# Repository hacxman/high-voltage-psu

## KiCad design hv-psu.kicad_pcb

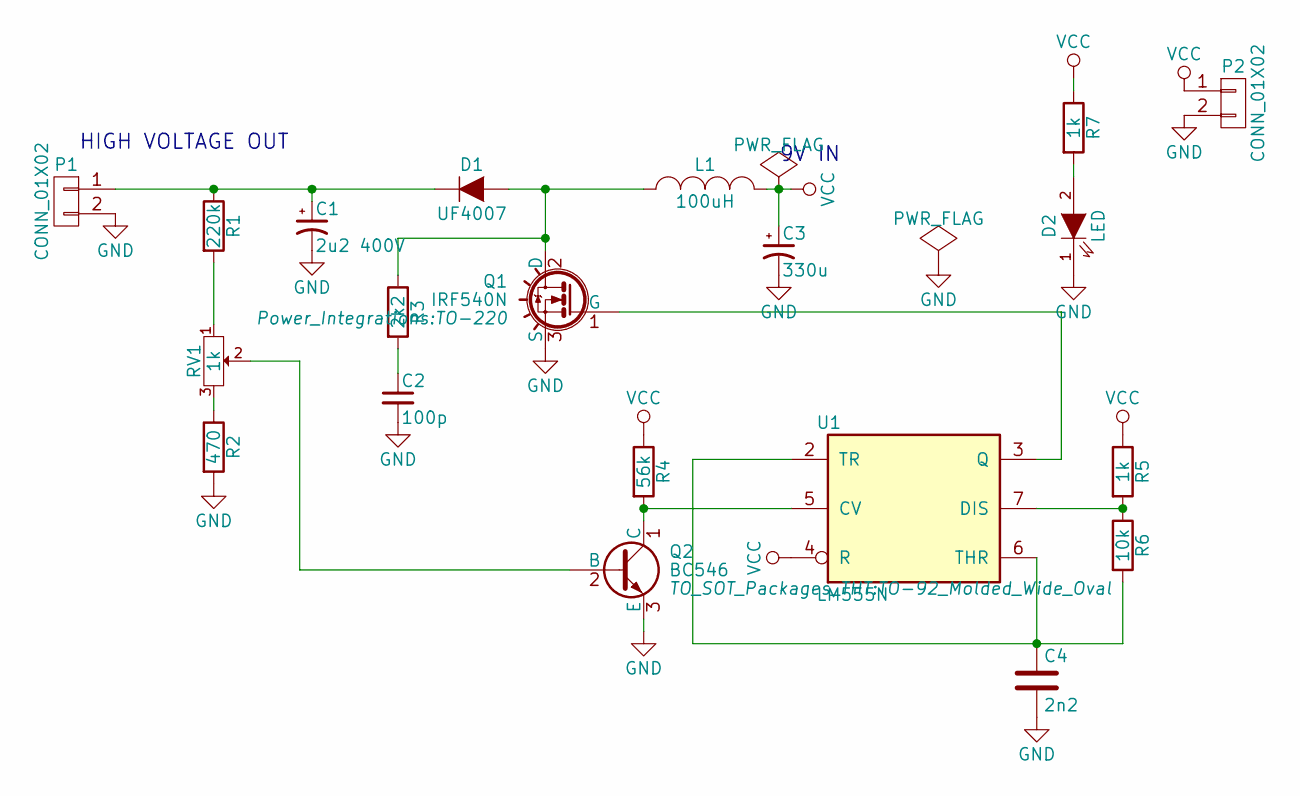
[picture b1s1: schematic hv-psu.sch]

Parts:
C1: 2u2 400V; C_Radial_D14_L31.5_P5
C2: 100p; C_Rect_L7_W2.5_P5
C3: 330u; C_Radial_D14_L31.5_P5
C4: 2n2; C_Rect_L7_W2.5_P5
D1: UF4007; Diode_DO-35_SOD27_Horizontal_RM10
D2: LED; LED-5MM
L1: 100uH; Choke_SMD_10.4x10.4_H4.8
P1, P2: CONN_01X02; TerminalBlock_Pheonix_MPT-2.54mm_2pol
Q1: IRF540N; TO-220
Q2: BC546; TO-92_Molded_Wide_Oval
R1: 220k; Resistor_Horizontal_RM10mm
R2: 470; Resistor_Horizontal_RM10mm
R3: 2k2; Resistor_Horizontal_RM10mm
R4: 56k; Resistor_Horizontal_RM10mm
R5, R7: 1k; Resistor_Horizontal_RM10mm
R6: 10k; Resistor_Horizontal_RM10mm
RV1: 1k; Potentiometer_WirePads_largePads
U1: LM555N; DIP-8_W7.62mm_LongPads

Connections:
GND: C1.2, C2.2, C3.2, C4.2, D2.1 (K), P1.2, P2.2, Q1.3 (S), Q2.3 (E), R2.2, U1.1 (GND)
unnamed: C1.1, D1.1 (K), P1.1, R1.1
unnamed: C2.1, R3.2
unnamed: C4.1, R6.2, U1.2 (TR), U1.6 (THR)
unnamed: D1.2 (A), L1.1, Q1.2 (D), R3.1
unnamed: D2.2 (A), R7.2
unnamed: Q1.1 (G), U1.3 (Q)
unnamed: Q2.1 (C), R4.2, U1.5 (CV)
unnamed: Q2.2 (B), RV1.2
unnamed: R1.2, RV1.1
unnamed: R2.1, RV1.3
unnamed: R5.2, R6.1, U1.7 (DIS)
VCC: C3.1, L1.2, P2.1, R4.1, R5.1, R7.1, U1.4 (R), U1.8 (VCC)

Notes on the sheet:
HIGH VOLTAGE OUT
9V IN

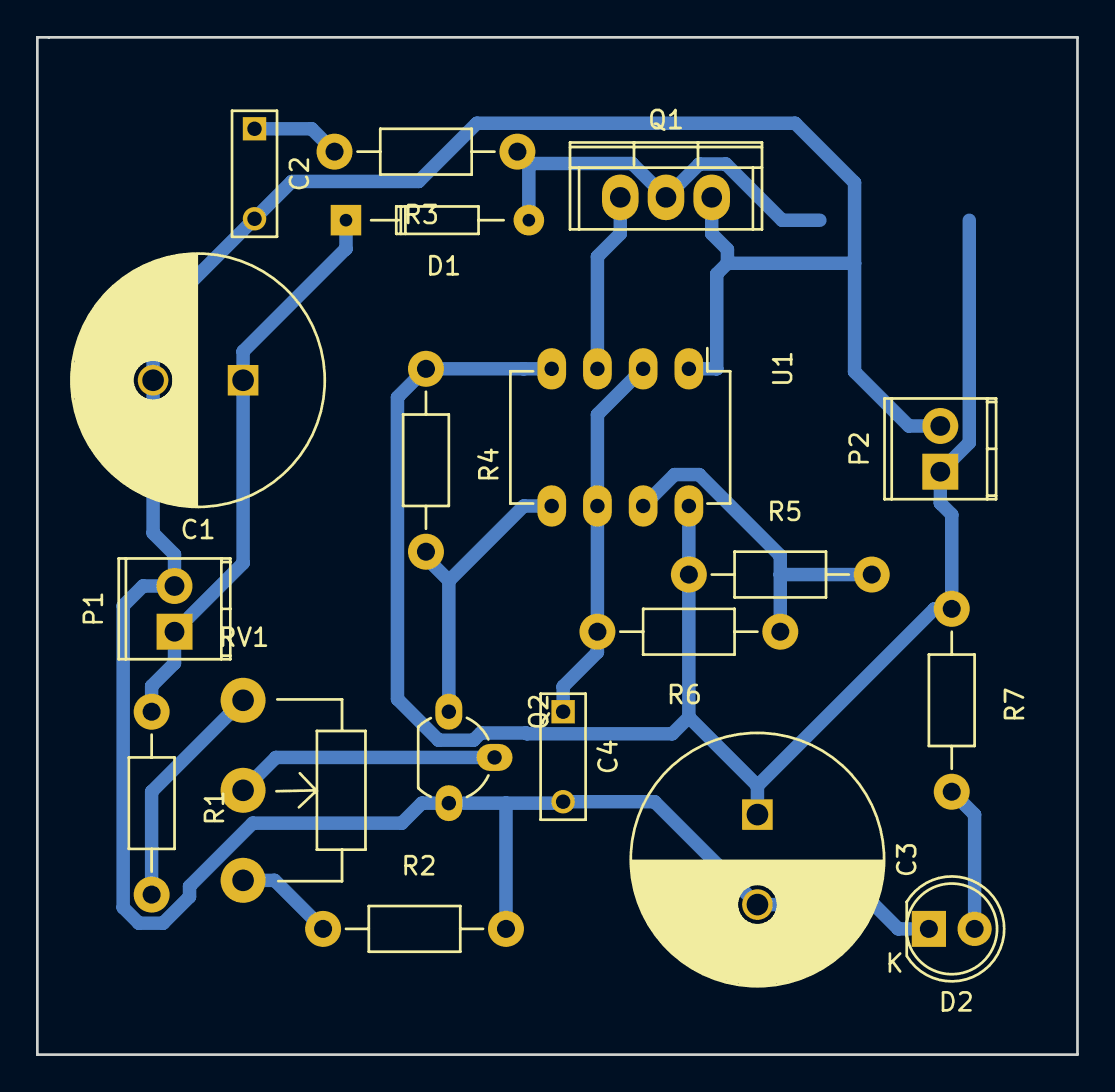
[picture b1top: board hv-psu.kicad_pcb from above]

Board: 2 copper layers, 57.8 x 56.5 mm, 20 parts (1 on the bottom side), 13 nets.

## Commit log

2016-09-29 first
2016-09-29 ltspice simulation
